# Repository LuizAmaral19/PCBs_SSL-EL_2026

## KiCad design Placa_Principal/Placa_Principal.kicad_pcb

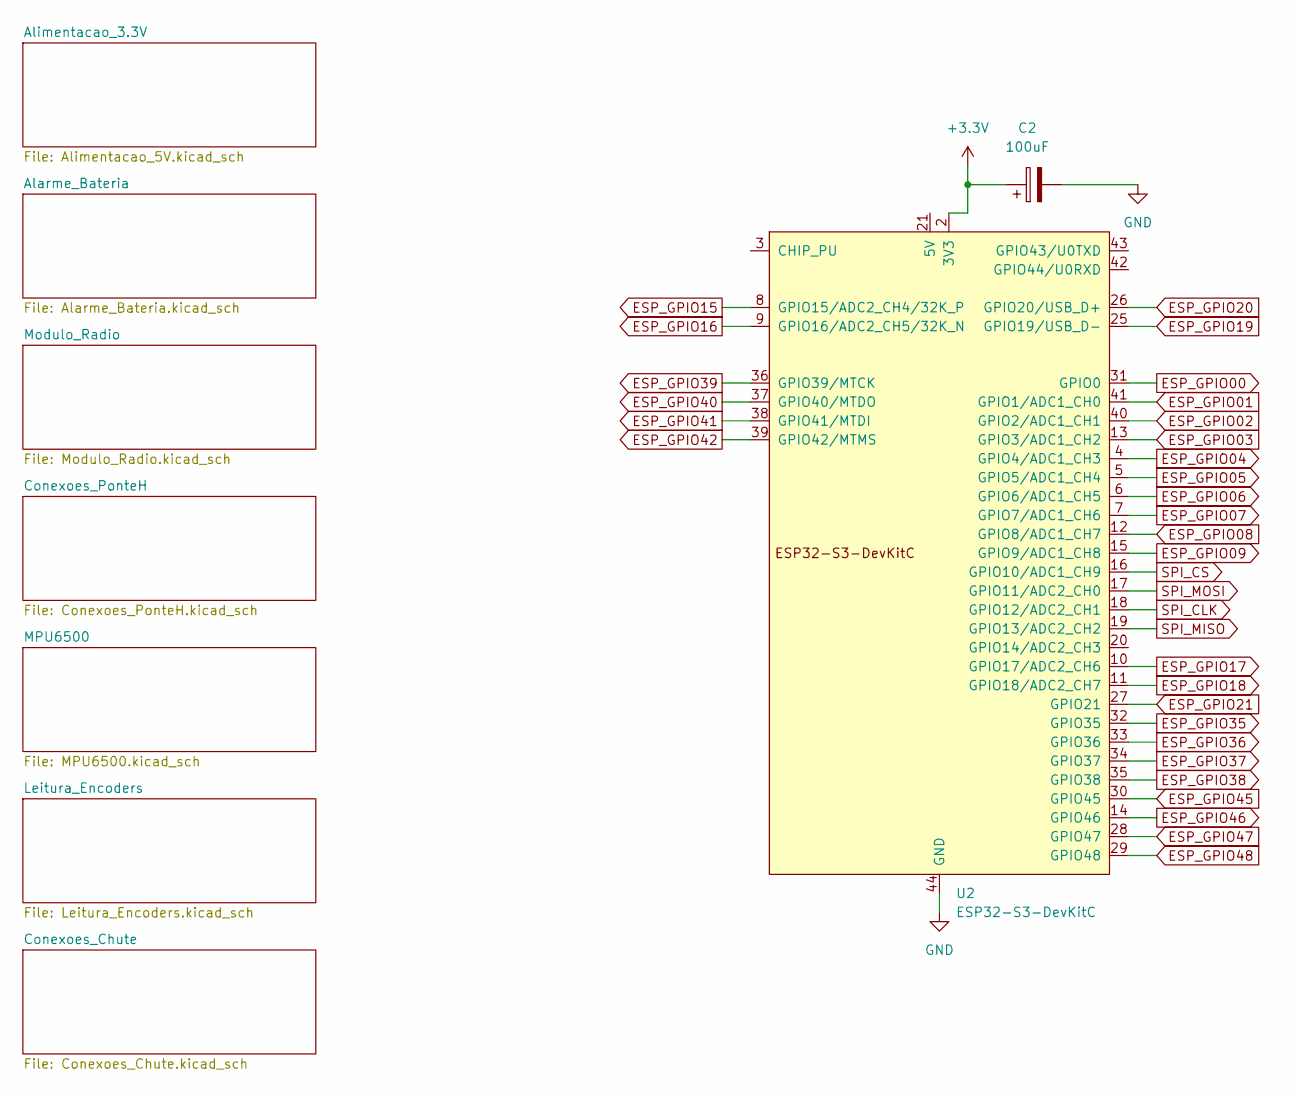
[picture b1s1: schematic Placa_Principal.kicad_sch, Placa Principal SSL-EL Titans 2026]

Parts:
C2: 100uF; CP_Radial_D8.0mm_P3.50mm
U2: ESP32-S3-DevKitC

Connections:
+3.3V: C2.1, U2.1 (3V3), U2.2 (3V3); also elsewhere on the board
ESP_GPIO00: U2.31 (GPIO0); also elsewhere on the board
ESP_GPIO01: U2.41 (GPIO1/ADC1_CH0); also elsewhere on the board
ESP_GPIO02: U2.40 (GPIO2/ADC1_CH1); also elsewhere on the board
ESP_GPIO03: U2.13 (GPIO3/ADC1_CH2); also elsewhere on the board
ESP_GPIO04: U2.4 (GPIO4/ADC1_CH3); also elsewhere on the board
ESP_GPIO05: U2.5 (GPIO5/ADC1_CH4); also elsewhere on the board
ESP_GPIO06: U2.6 (GPIO6/ADC1_CH5); also elsewhere on the board
ESP_GPIO07: U2.7 (GPIO7/ADC1_CH6); also elsewhere on the board
ESP_GPIO08: U2.12 (GPIO8/ADC1_CH7); also elsewhere on the board
ESP_GPIO09: U2.15 (GPIO9/ADC1_CH8); also elsewhere on the board
ESP_GPIO15: U2.8 (GPIO15/ADC2_CH4/32K_P); also elsewhere on the board
ESP_GPIO16: U2.9 (GPIO16/ADC2_CH5/32K_N); also elsewhere on the board
ESP_GPIO17: U2.10 (GPIO17/ADC2_CH6); also elsewhere on the board
ESP_GPIO18: U2.11 (GPIO18/ADC2_CH7); also elsewhere on the board
ESP_GPIO19: U2.25 (GPIO19/USB_D-); also elsewhere on the board
ESP_GPIO20: U2.26 (GPIO20/USB_D+); also elsewhere on the board
ESP_GPIO21: U2.27 (GPIO21); also elsewhere on the board
ESP_GPIO35: U2.32 (GPIO35); also elsewhere on the board
ESP_GPIO36: U2.33 (GPIO36); also elsewhere on the board
ESP_GPIO37: U2.34 (GPIO37); also elsewhere on the board
ESP_GPIO38: U2.35 (GPIO38); also elsewhere on the board
ESP_GPIO39: U2.36 (GPIO39/MTCK); also elsewhere on the board
ESP_GPIO40: U2.37 (GPIO40/MTDO); also elsewhere on the board
ESP_GPIO41: U2.38 (GPIO41/MTDI); also elsewhere on the board
ESP_GPIO42: U2.39 (GPIO42/MTMS); also elsewhere on the board
ESP_GPIO45: U2.30 (GPIO45); also elsewhere on the board
ESP_GPIO46: U2.14 (GPIO46); also elsewhere on the board
ESP_GPIO47: U2.28 (GPIO47); also elsewhere on the board
ESP_GPIO48: U2.29 (GPIO48); also elsewhere on the board
GND: C2.2, U2.22 (GND), U2.23 (GND), U2.24 (GND), U2.44 (GND); also elsewhere on the board
SPI_CLK: U2.18 (GPIO12/ADC2_CH1)
SPI_CS: U2.16 (GPIO10/ADC1_CH9)
SPI_MISO: U2.19 (GPIO13/ADC2_CH2)
SPI_MOSI: U2.17 (GPIO11/ADC2_CH0)

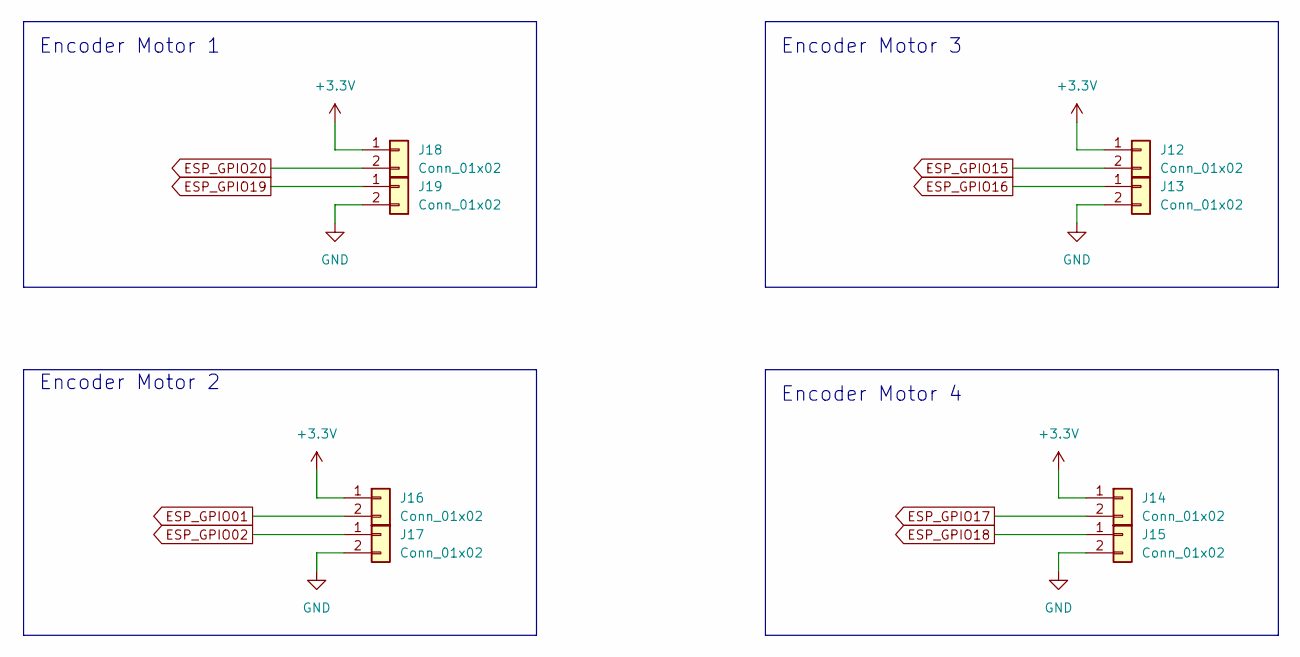
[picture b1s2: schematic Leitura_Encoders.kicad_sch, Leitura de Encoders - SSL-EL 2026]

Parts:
J12, J13, J14, J15, J16, J17, J18, J19: Conn_01x02; Molex_KK-254_AE-6410-02A_1x02_P2.54mm_Vertical

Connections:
+3.3V: J12.1, J14.1, J16.1, J18.1; also elsewhere on the board
ESP_GPIO01: J16.2; also elsewhere on the board
ESP_GPIO02: J17.1; also elsewhere on the board
ESP_GPIO15: J12.2; also elsewhere on the board
ESP_GPIO16: J13.1; also elsewhere on the board
ESP_GPIO17: J14.2; also elsewhere on the board
ESP_GPIO18: J15.1; also elsewhere on the board
ESP_GPIO19: J19.1; also elsewhere on the board
ESP_GPIO20: J18.2; also elsewhere on the board
GND: J13.2, J15.2, J17.2, J19.2; also elsewhere on the board

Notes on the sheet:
Encoder Motor 4
Encoder Motor 1
Encoder Motor 2
Encoder Motor 3

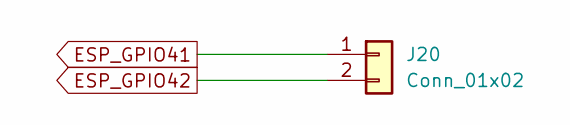
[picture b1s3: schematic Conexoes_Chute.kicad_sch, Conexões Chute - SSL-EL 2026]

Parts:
J20: Conn_01x02; Molex_KK-254_AE-6410-02A_1x02_P2.54mm_Vertical

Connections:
ESP_GPIO41: J20.1; also elsewhere on the board
ESP_GPIO42: J20.2; also elsewhere on the board

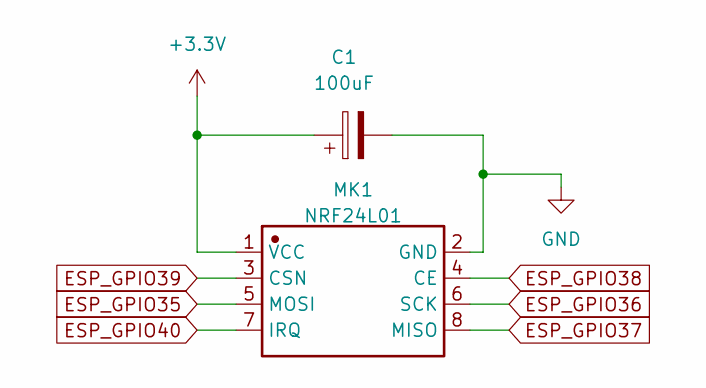
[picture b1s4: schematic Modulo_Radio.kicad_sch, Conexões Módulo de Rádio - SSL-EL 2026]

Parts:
C1: 100uF; CP_Radial_D8.0mm_P3.50mm
MK1: NRF24L01; nRF24L01; Manufacturer Part NF-04

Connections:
+3.3V: C1.1, MK1.1 (VCC); also elsewhere on the board
ESP_GPIO35: MK1.5 (MOSI); also elsewhere on the board
ESP_GPIO36: MK1.6 (SCK); also elsewhere on the board
ESP_GPIO37: MK1.8 (MISO); also elsewhere on the board
ESP_GPIO38: MK1.4 (CE); also elsewhere on the board
ESP_GPIO39: MK1.3 (CSN); also elsewhere on the board
ESP_GPIO40: MK1.7 (IRQ); also elsewhere on the board
GND: C1.2, MK1.2 (GND); also elsewhere on the board

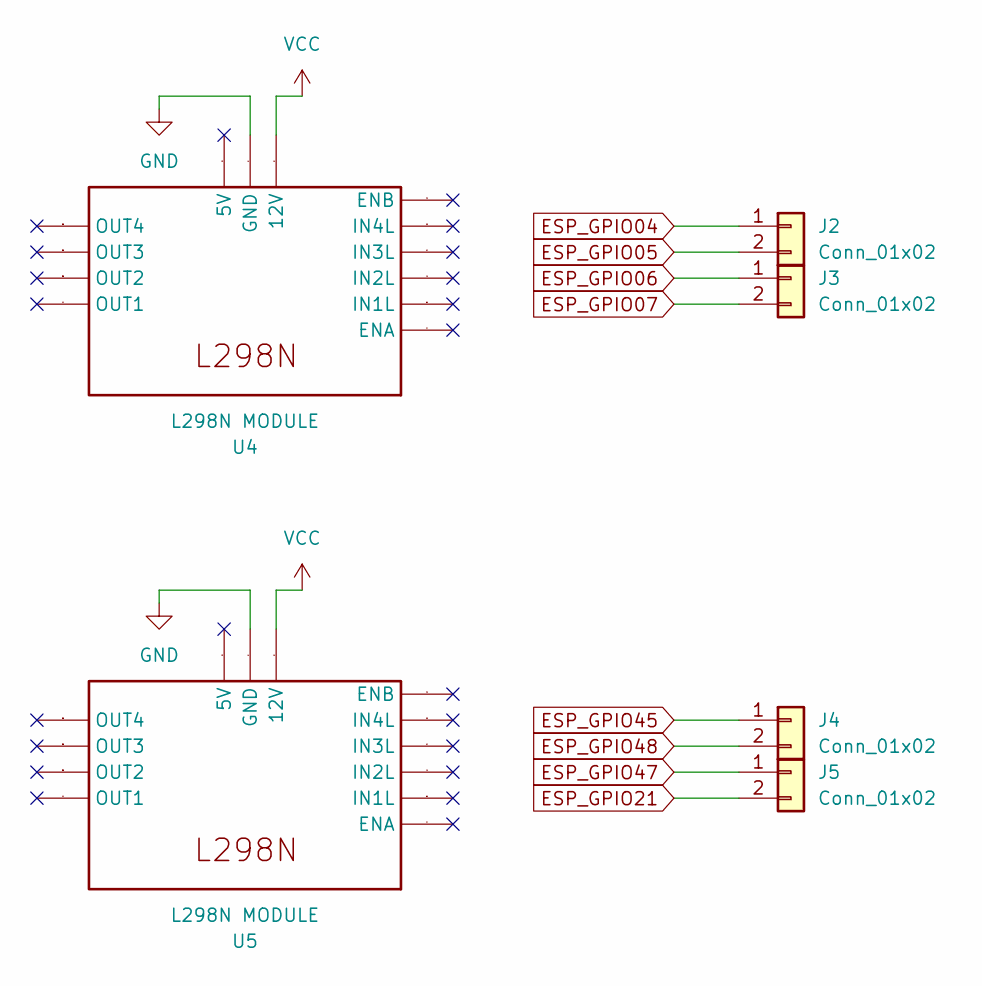
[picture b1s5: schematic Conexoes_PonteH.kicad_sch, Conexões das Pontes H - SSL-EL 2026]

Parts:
J2, J3, J4, J5: Conn_01x02; Molex_KK-254_AE-6410-02A_1x02_P2.54mm_Vertical
U4, U5: L298N MODULE; L298N Module

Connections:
ESP_GPIO04: J2.1; also elsewhere on the board
ESP_GPIO05: J2.2; also elsewhere on the board
ESP_GPIO06: J3.1; also elsewhere on the board
ESP_GPIO07: J3.2; also elsewhere on the board
ESP_GPIO21: J5.2; also elsewhere on the board
ESP_GPIO45: J4.1; also elsewhere on the board
ESP_GPIO47: J5.1; also elsewhere on the board
ESP_GPIO48: J4.2; also elsewhere on the board
GND: U4.7 (GND), U5.7 (GND); also elsewhere on the board
VCC: U4.6 (12V), U5.6 (12V); also elsewhere on the board

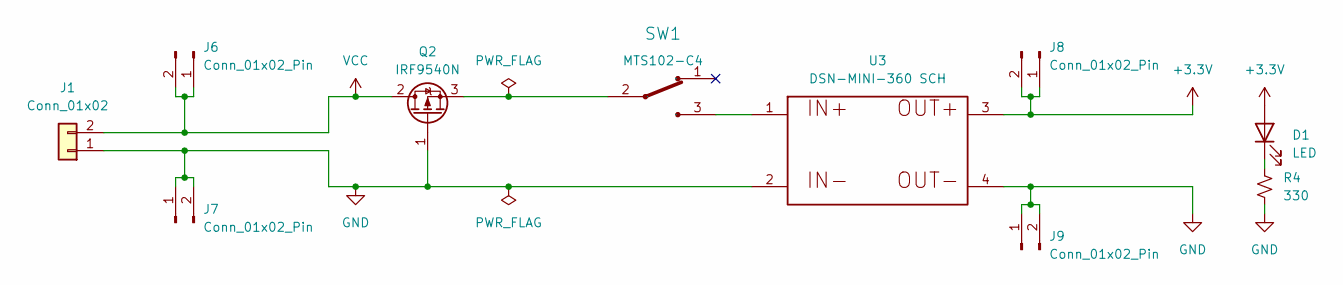
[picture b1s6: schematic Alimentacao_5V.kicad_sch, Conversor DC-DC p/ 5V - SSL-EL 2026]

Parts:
D1: LED; LED_D10.0mm
J1: Conn_01x02; AMASS_XT30UPB-M_1x02_P5.0mm_Vertical
J6, J7, J8, J9: Conn_01x02_Pin; PinHeader_1x02_P2.54mm_Vertical
Q2: IRF9540N; TO-220-3_Vertical
R4: 330; R_Axial_DIN0204_L3.6mm_D1.6mm_P5.08mm_Horizontal
SW1: MTS102-C4
U3: DSN-MINI-360 SCH; DSN-MINI-360

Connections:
+3.3V: D1.2 (A), J8.1, J8.2, U3.3; also elsewhere on the board
GND: J1.1, J7.1, J7.2, J9.1, J9.2, Q2.1 (G), R4.2, U3.2, U3.4; also elsewhere on the board
unnamed: D1.1 (K), R4.1
unnamed: Q2.3 (S), SW1.2
unnamed: SW1.3, U3.1
VCC: J1.2, J6.1, J6.2, Q2.2 (D); also elsewhere on the board

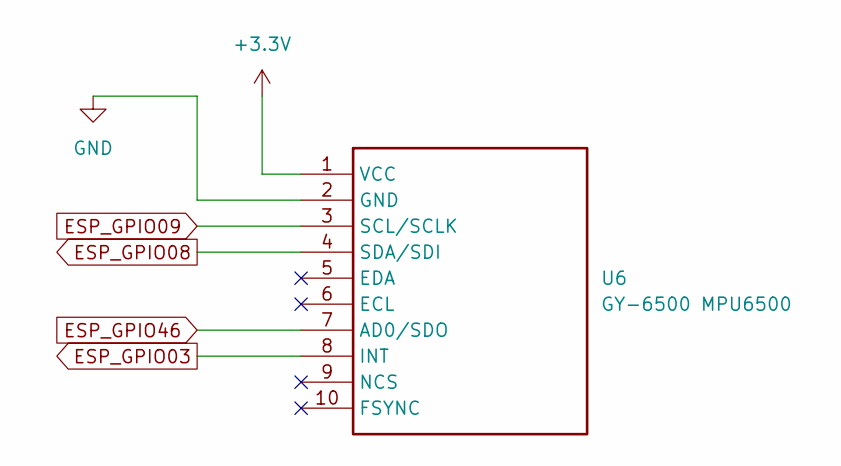
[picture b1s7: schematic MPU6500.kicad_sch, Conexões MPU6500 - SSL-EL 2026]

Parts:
U6: GY-6500 MPU6500

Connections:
+3.3V: U6.1 (VCC); also elsewhere on the board
ESP_GPIO03: U6.8 (INT); also elsewhere on the board
ESP_GPIO08: U6.4 (SDA/SDI); also elsewhere on the board
ESP_GPIO09: U6.3 (SCL/SCLK); also elsewhere on the board
ESP_GPIO46: U6.7 (AD0/SDO); also elsewhere on the board
GND: U6.2 (GND); also elsewhere on the board

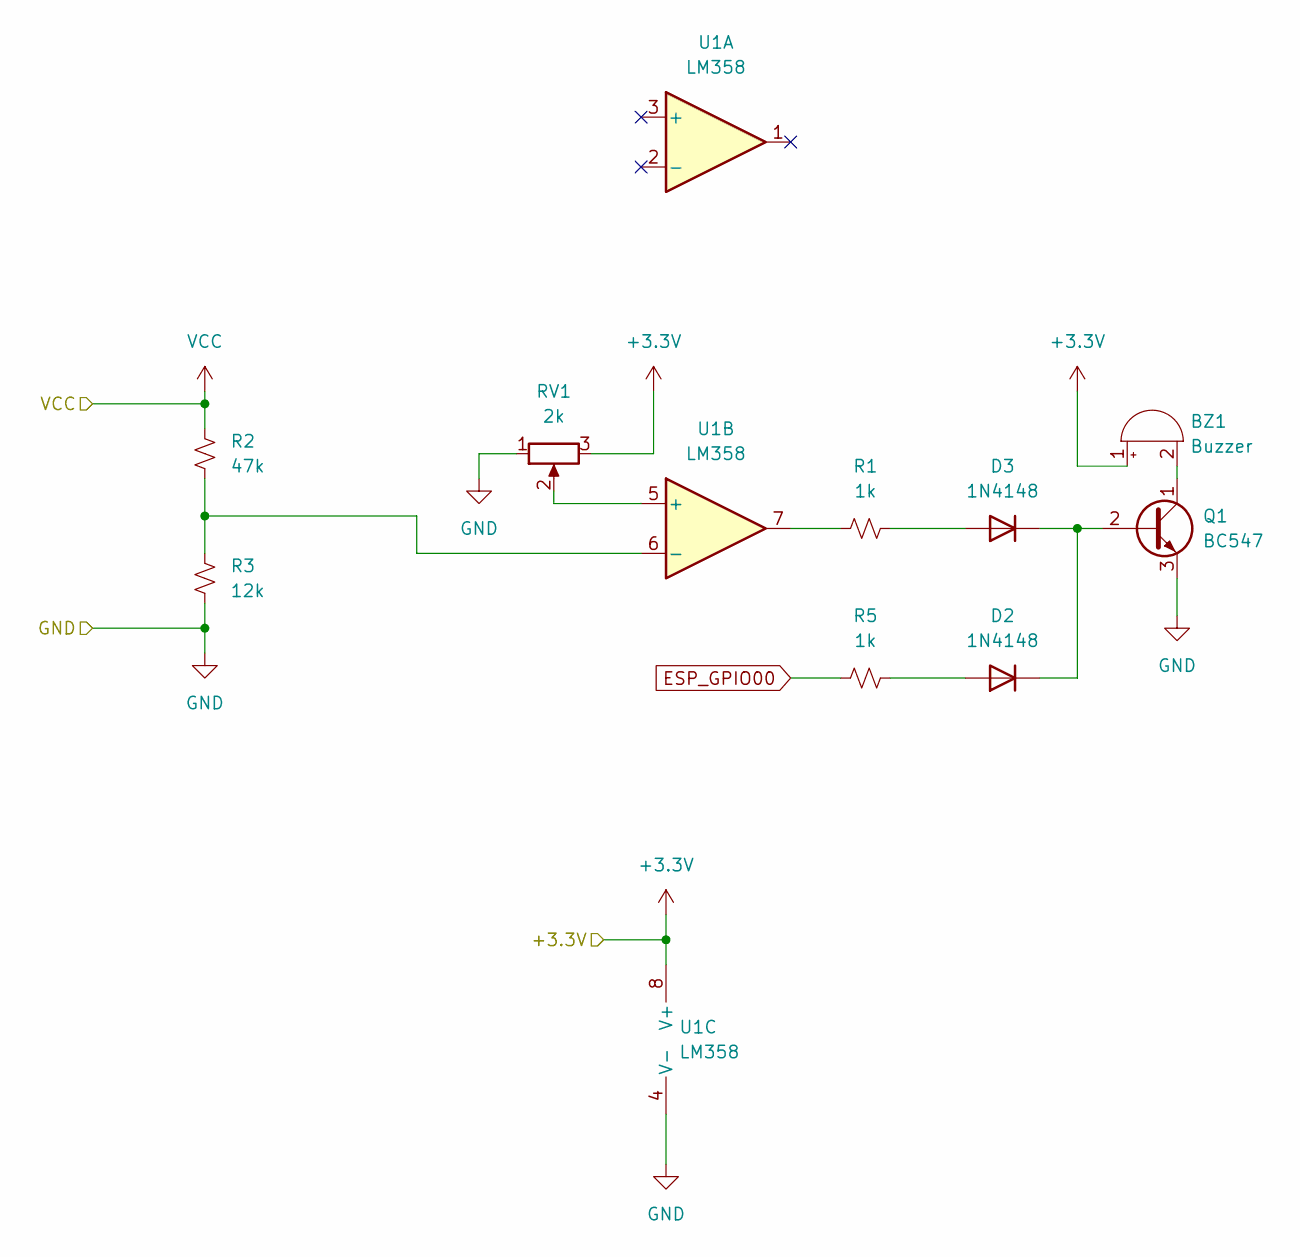
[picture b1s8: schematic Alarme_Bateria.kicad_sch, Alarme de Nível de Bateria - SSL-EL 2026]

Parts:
BZ1: Buzzer; Buzzer_12x9.5RM7.6
D2, D3: 1N4148; D_DO-35_SOD27_P7.62mm_Horizontal
Q1: BC547; TO-92_Inline
R1, R5: 1k; R_Axial_DIN0204_L3.6mm_D1.6mm_P5.08mm_Horizontal
R2: 47k; R_Axial_DIN0204_L3.6mm_D1.6mm_P5.08mm_Horizontal
R3: 12k; R_Axial_DIN0204_L3.6mm_D1.6mm_P5.08mm_Horizontal
RV1: 2k; RTRIM3362P
U1: LM358; DIP-8_W7.62mm_Socket

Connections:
+3.3V: BZ1.1 (+), RV1.3, U1.8 (V+); also elsewhere on the board
ESP_GPIO00: R5.1; also elsewhere on the board
GND: Q1.3 (E), R3.2, RV1.1, U1.4 (V-); also elsewhere on the board
unnamed: BZ1.2 (-), Q1.1 (C)
unnamed: D2.2 (A), R5.2
unnamed: D2.1 (K), D3.1 (K), Q1.2 (B)
unnamed: D3.2 (A), R1.2
unnamed: R1.1, U1.7
unnamed: RV1.2, U1.5 (+)
unnamed: R2.2, R3.1, U1.6 (-)
VCC: R2.1; also elsewhere on the board

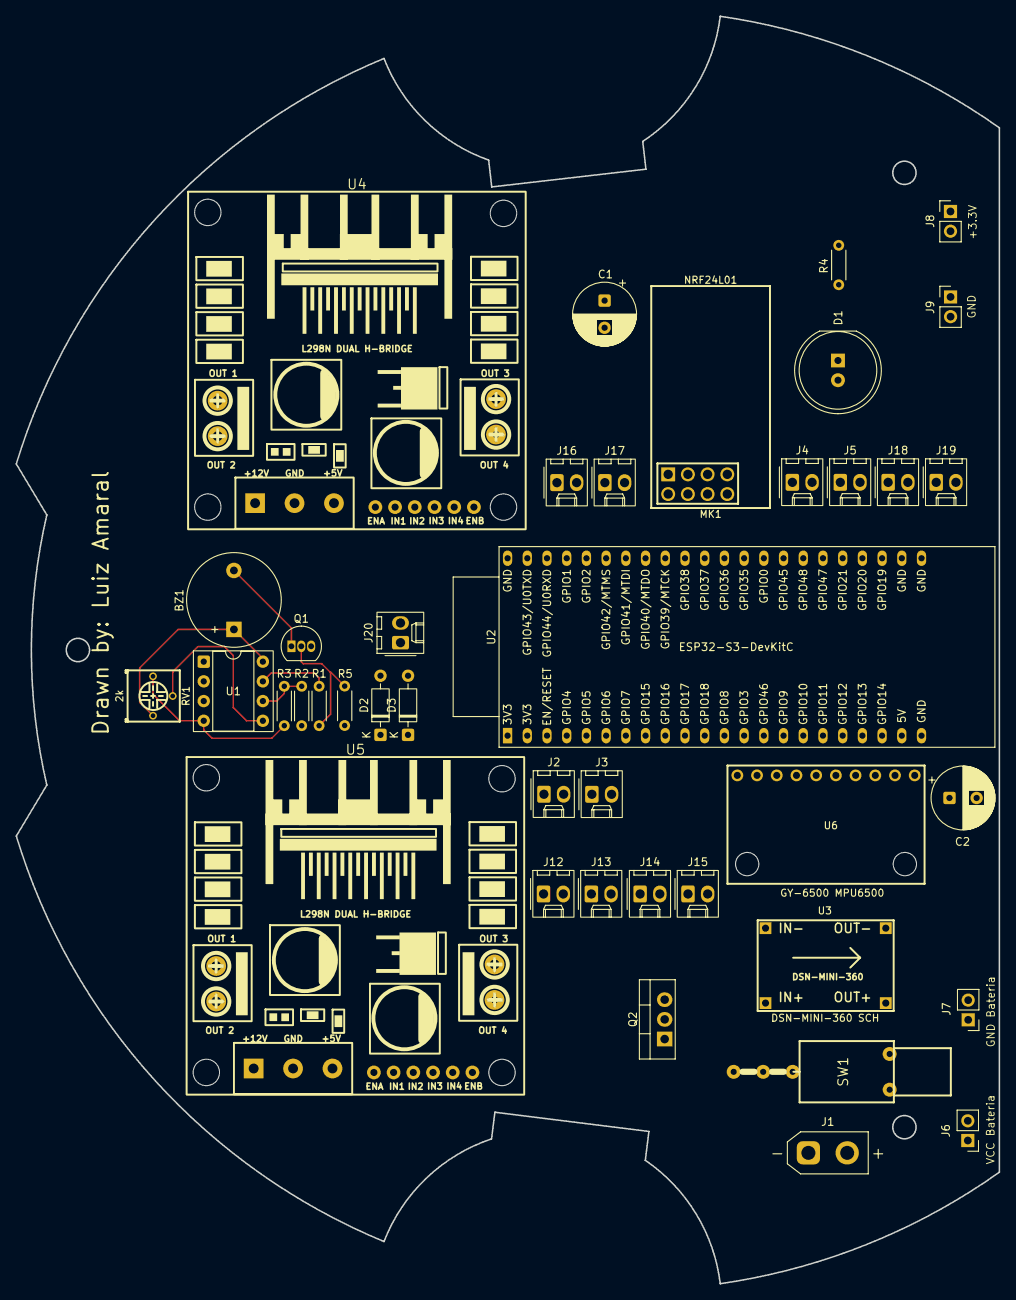
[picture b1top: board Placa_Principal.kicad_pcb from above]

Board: 2 copper layers, 126.7 x 163.3 mm, 40 parts (0 on the bottom side), 42 nets.

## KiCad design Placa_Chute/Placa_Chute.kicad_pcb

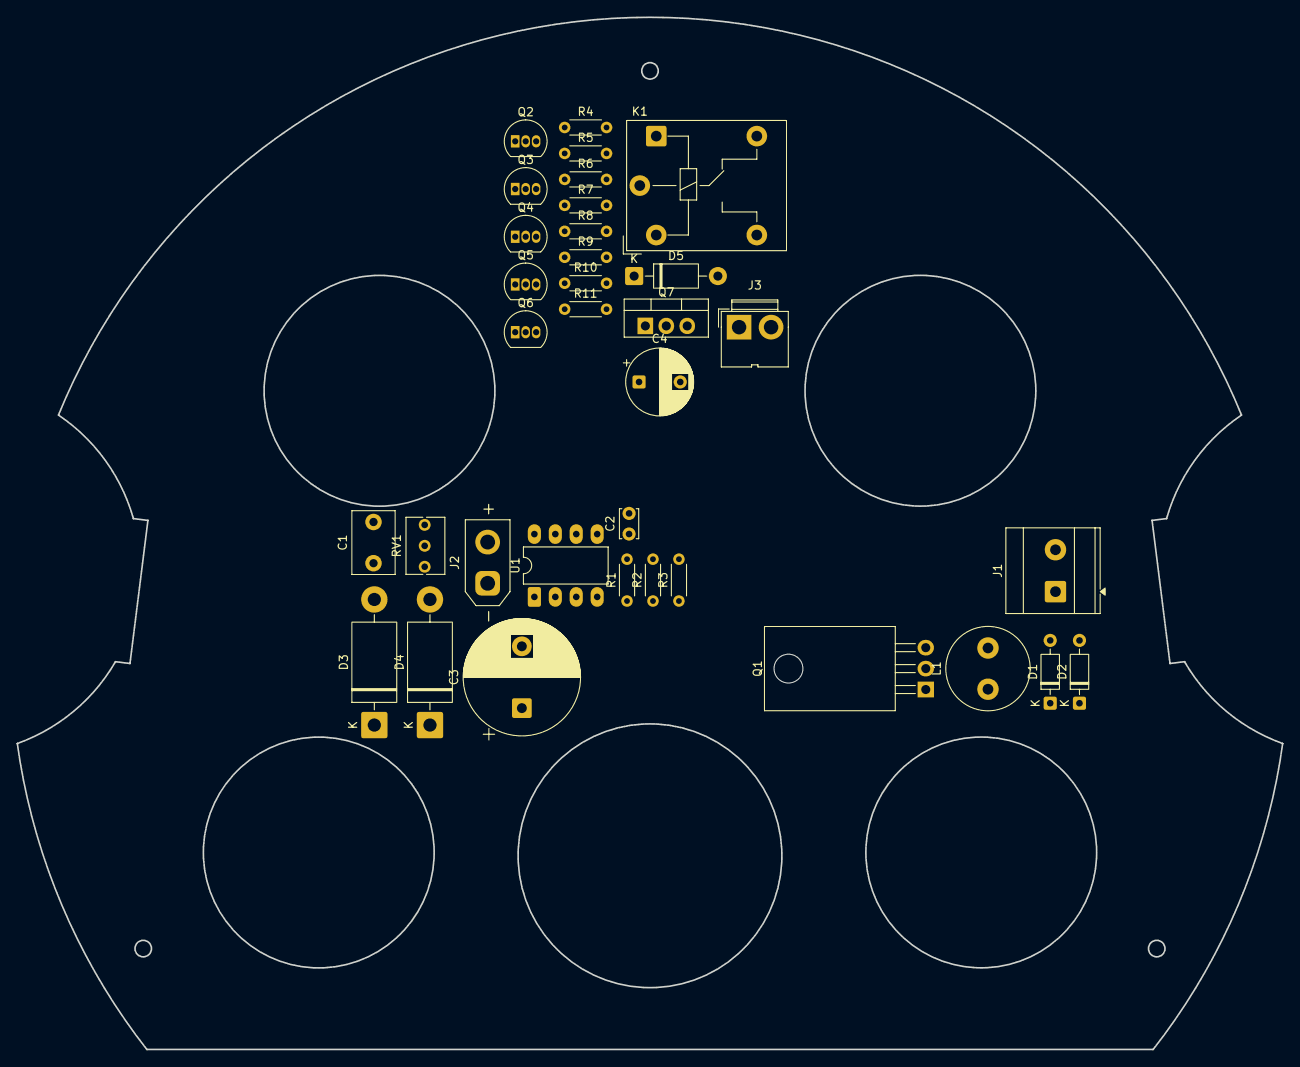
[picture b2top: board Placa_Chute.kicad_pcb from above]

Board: 2 copper layers, 153.5 x 125.2 mm, 34 parts (0 on the bottom side), 24 nets, no tracks yet.

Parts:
C1: 2.2nF; C_Disc_D7.5mm_W5.0mm_P5.00mm
C2: 100nF; C_Disc_D3.4mm_W2.1mm_P2.50mm
C3: 220uF; CP_Radial_D14.0mm_P7.50mm
C4: 1000uF; CP_Radial_D8.0mm_P5.00mm
D1, D2: 1N4148; D_DO-35_SOD27_P7.62mm_Horizontal
D3, D4: UF5408; D_DO-201AD_P15.24mm_Horizontal
D5: 1N4007; D_DO-41_SOD81_P10.16mm_Horizontal
J1: Screw_Terminal_01x02; TerminalBlock_Phoenix_MKDS-3-2-5.08_1x02_P5.08mm_Horizontal
J2: Conn_01x02_Socket; AMASS_XT30UPB-M_1x02_P5.0mm_Vertical
J3: Conn_01x02; JWT_A3963_1x02_P3.96mm_Vertical
K1: JQC-3FF-012-1Z; Relay_SPDT_Hongfa_JQC-3FF_0XX-1Z
L1: 400uH; L_Radial_D10.0mm_P5.00mm_Fastron_07M
Q1: IRF630; TO-220-3_Horizontal_TabDown
Q2, Q4, Q5: BC337; TO-92_Inline
Q3: BC547; TO-92_Inline
Q6: BC327; TO-92_Inline
Q7: IRFZ44N; TO-220-3_Vertical
R1: 47K; R_Axial_DIN0204_L3.6mm_D1.6mm_P5.08mm_Horizontal
R2, R10: 100; R_Axial_DIN0204_L3.6mm_D1.6mm_P5.08mm_Horizontal
R3, R8, R9: 10K; R_Axial_DIN0204_L3.6mm_D1.6mm_P5.08mm_Horizontal
R4: 300; R_Axial_DIN0204_L3.6mm_D1.6mm_P5.08mm_Horizontal
R5: 1K; R_Axial_DIN0204_L3.6mm_D1.6mm_P5.08mm_Horizontal
R6, R7: 2.2K; R_Axial_DIN0204_L3.6mm_D1.6mm_P5.08mm_Horizontal
R11: 10; R_Axial_DIN0204_L3.6mm_D1.6mm_P5.08mm_Horizontal
RV1: 100K; Potentiometer_Bourns_3266Y_Vertical
U1: NE555P; DIP-8_W7.62mm_LongPads

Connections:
+12V: D5.1 (K), K1.A2, Q5.1 (C), R5.2, R8.2
/Circuito_Boost/V_out: C3.1, D4.1 (K), J1.1
GND: C1.2, C2.2, C3.2, C4.2, J1.2, J2.2, Q1.3 (S), Q2.3 (E), Q3.3 (E), Q4.3 (E), Q6.3 (E), Q7.3 (S), R3.1, R9.1, U1.1 (GND)
unnamed: D1.2 (A), RV1.1
unnamed: D1.1 (K), D2.2 (A), R1.1, U1.7 (DISCH)
unnamed: D2.1 (K), RV1.3
unnamed: D3.1 (K), L1.1
unnamed: D4.2 (A), L1.2, Q1.2 (D)
unnamed: D5.2 (A), K1.A1, Q3.1 (C)
unnamed: C4.1, J3.1, R11.2
unnamed: J3.2, Q7.1 (D)
unnamed: K1.14, R11.1
unnamed: Q1.1 (G), R2.2, R3.2
unnamed: Q2.2 (B), R4.2
unnamed: Q2.1 (C), R5.1, R6.1, R7.1
unnamed: Q3.2 (B), R6.2
unnamed: Q4.2 (B), R7.2
unnamed: Q4.1 (C), Q5.2 (B), Q6.2 (B), R8.1
unnamed: Q5.3 (E), Q6.1 (C), R9.2, R10.2
unnamed: Q7.2 (G), R10.1
unnamed: C2.1, U1.5 (CONT)
unnamed: R2.1, U1.3 (OUT)
unnamed: C1.1, RV1.2, U1.2 (TRIG), U1.6 (THRES)
VCC: D3.2 (A), J2.1, R1.2, U1.4 (~RST), U1.8 (VCC)

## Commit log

2026-05-14 Primeiro commit
2026-05-20 Segundo commit
2026-05-21 Apagar o esquemático de Ativação de Chute
2026-05-22 Finalizando o esquemático e rearranjando a posição dos componentes na PCB
2026-05-23 Atualizando a alimentação de todos os sensores e ESP para 3.3V e finalizando o design do monitoramento da bateria e feedback geral
2026-05-27 Atualizações do esquemático Root
